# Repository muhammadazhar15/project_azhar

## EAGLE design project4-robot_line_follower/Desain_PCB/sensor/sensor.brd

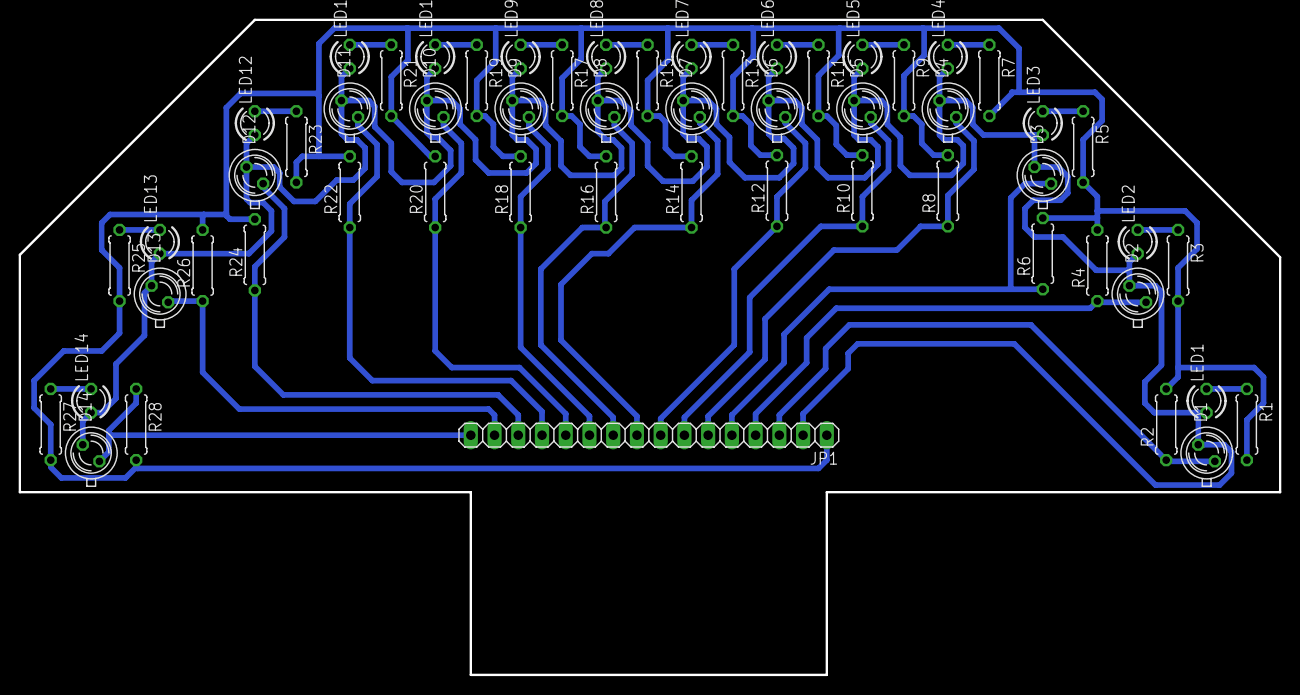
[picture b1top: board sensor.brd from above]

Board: 2 copper layers, 134.9 x 70.1 mm, 57 parts (0 on the bottom side), 30 nets.

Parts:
D1, D2, D3, D4, D5, D6, D7, D8, D9, D10, D11, D12, D13, D14: BPX65
JP1: 1X16
LED1, LED2, LED3, LED4, LED5, LED6, LED7, LED8, LED9, LED10, LED11, LED12, LED13, LED14: LED3MM
R1, R3, R5, R7, R9, R11, R13, R15, R17, R19, R21, R23, R25, R27: 470; 0207/7
R2, R4, R6, R8, R10, R12, R14, R16, R18, R20, R22, R24, R26, R28: 22K; 0207/7

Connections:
1: D1.A, JP1.3, R2.1
2: D2.A, JP1.4, R4.1
3: D3.A, JP1.5, R6.1
4: D4.A, JP1.6, R8.1
5: D5.A, JP1.7, R10.1
5V: D1.K, D2.K, D3.K, D4.K, D5.K, D6.K, D7.K, D8.K, D9.K, D10.K, D11.K, D12.K, D13.K, D14.K, JP1.2, LED1.A, LED2.A, LED3.A, LED4.A, LED5.A, LED6.A, LED7.A, LED8.A, LED9.A, LED10.A, LED11.A, LED12.A, LED13.A, LED14.A
6: D6.A, JP1.8, R12.1
7: D7.A, JP1.9, R14.1
8: D8.A, JP1.10, R16.1
9: D9.A, JP1.11, R18.1
10: D10.A, JP1.12, R20.1
11: D11.A, JP1.13, R22.1
12: D12.A, JP1.14, R24.1
13: D13.A, JP1.15, R26.1
14: D14.A, JP1.16, R28.1
GND: JP1.1, R1.2, R2.2, R3.2, R4.2, R5.2, R6.2, R7.2, R8.2, R9.2, R10.2, R11.2, R12.2, R13.2, R14.2, R15.2, R16.2, R17.2, R18.2, R19.2, R20.2, R21.2, R22.2, R23.2, R24.2, R25.2, R26.2, R27.2, R28.2
unnamed: LED1.K, R1.1
unnamed: LED2.K, R3.1
unnamed: LED3.K, R5.1
unnamed: LED4.K, R7.1
unnamed: LED5.K, R9.1
unnamed: LED6.K, R11.1
unnamed: LED7.K, R13.1
unnamed: LED8.K, R15.1
unnamed: LED9.K, R17.1
unnamed: LED10.K, R19.1
unnamed: LED11.K, R21.1
unnamed: LED12.K, R23.1
unnamed: LED13.K, R25.1
unnamed: LED14.K, R27.1
